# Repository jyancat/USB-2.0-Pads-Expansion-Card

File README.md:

# USB 2.0 Pads Expansion Card
 This is a repository for files for the USB 2.0 Pads expansion card. This breaks out standard USB 2.0 signals to 4 SMD pads.
 Untested.

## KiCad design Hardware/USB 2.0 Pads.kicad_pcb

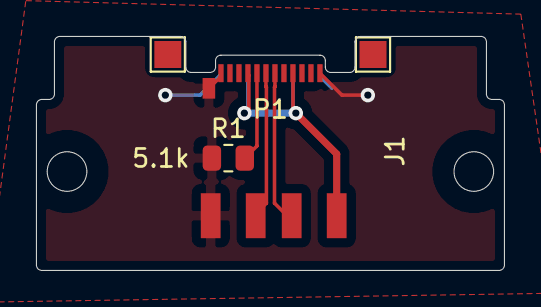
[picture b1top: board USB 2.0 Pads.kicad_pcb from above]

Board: 2 copper layers, 26.0 x 13.0 mm, 7 parts (0 on the bottom side), 5 nets.

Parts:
H1, H2: MountingHole; MountingHole_2.2mm_M2
J1: USB_A; USB-PADS
P1: USB_C_Plug_USB2.0; USB_C_Plug_Molex_105444
R1: 5.1k; R_0805_2012Metric
TP1, TP3: TestPoint; TestPoint_Pad_1.5x1.5mm

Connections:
D+: J1.3, P1.A6
D-: J1.2, P1.A7
unnamed: J1.1, P1.A4, P1.A9, P1.B4, P1.B9
unnamed: J1.4, P1.A1, P1.A12, P1.B1, P1.B12, P1.S1, R1.1
unnamed: P1.A5, R1.2

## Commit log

2022-05-03 Added new files.
2022-05-03 Updated files
